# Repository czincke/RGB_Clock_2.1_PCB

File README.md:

# RGB_Clock_2.1_PCB
Updated RGB Clock using Adafruit products

Clock using four 7 segment RGB LEDs, three 24 channel PWM (TLC5973), RTC (DS3231), & Trinket (ATTiny85).

Materials:
* 1 x PCB
  * PCB	Clock_v2.1.brd
* 4 x RGB 7-Segment Digit
  * Product: https://www.adafruit.com/products/1399
* 3 x 24-Channel 12-bit PWM LED Driver (TLC5973)
  * Product: https://www.adafruit.com/products/1429
  * Tutorial: https://learn.adafruit.com/tlc5947-tlc59711-pwm-led-driver-breakout
* 1 x DS3231 Precision RTC Breakout
  * Product: https://www.adafruit.com/products/3013
  * Tutorial: https://learn.adafruit.com/adafruit-ds3231-precision-rtc-breakout/
* 1 x Adafruit Trinket - Mini Microcontroller - 5V Logic (ATTiny85)
  * Product: https://www.adafruit.com/products/1501
  * Tutorial: https://learn.adafruit.com/introducing-trinket

See: https://github.com/czincke/RGB_Clock_2.1_Code for Software Code.

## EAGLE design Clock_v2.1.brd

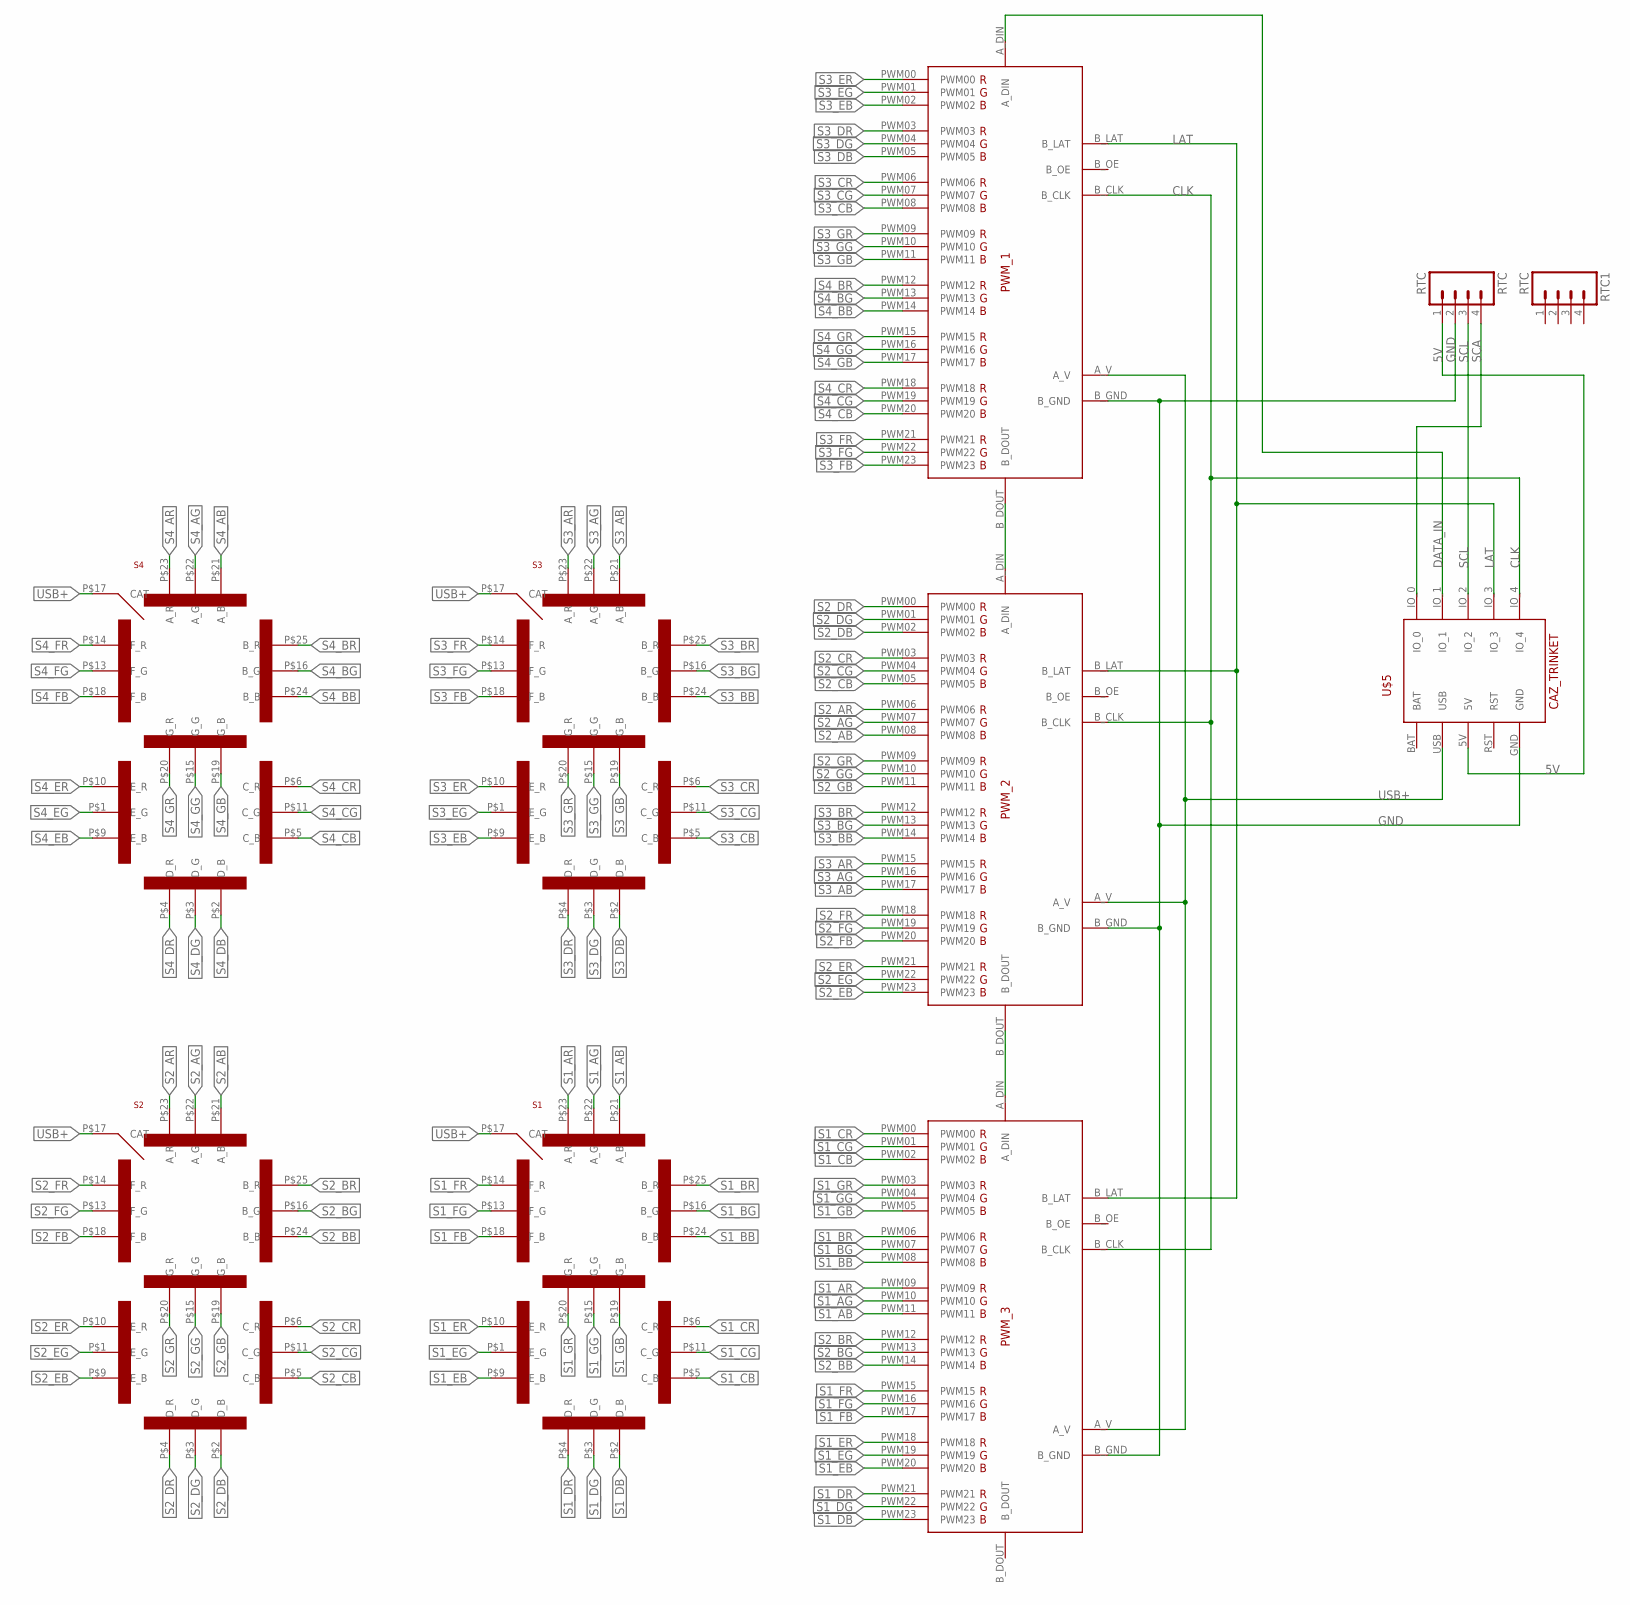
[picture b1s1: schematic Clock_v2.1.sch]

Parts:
PWM_1, PWM_2, PWM_3: CAZ_24PWM_DRIVER_MINIMAL
RTC, RTC1: RTC; 1X04_NO_SILK
S1, S2, S3, S4: CAZ_7SEGMENT_RGB_LEDBACKSIDE_MOUNT; CAZ_7SEGMENT_RGB_LED
U$5: CAZ_TRINKET

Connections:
5V: RTC.1, U$5.5V
CLK: PWM_1.B_CLK, PWM_2.B_CLK, PWM_3.B_CLK, U$5.IO_4
DATA_IN: PWM_1.A_DIN, U$5.IO_1
GND: PWM_1.B_GND, PWM_2.B_GND, PWM_3.B_GND, RTC.2, U$5.GND
LAT: PWM_1.B_LAT, PWM_2.B_LAT, PWM_3.B_LAT, U$5.IO_3
unnamed: PWM_1.B_DOUT, PWM_2.A_DIN
unnamed: PWM_2.B_DOUT, PWM_3.A_DIN
S1_AB: PWM_3.PWM11, S1.P$21 (A_B)
S1_AG: PWM_3.PWM10, S1.P$22 (A_G)
S1_AR: PWM_3.PWM09, S1.P$23 (A_R)
S1_BB: PWM_3.PWM08, S1.P$24 (B_B)
S1_BG: PWM_3.PWM07, S1.P$16 (B_G)
S1_BR: PWM_3.PWM06, S1.P$25 (B_R)
S1_CB: PWM_3.PWM02, S1.P$5 (C_B)
S1_CG: PWM_3.PWM01, S1.P$11 (C_G)
S1_CR: PWM_3.PWM00, S1.P$6 (C_R)
S1_DB: PWM_3.PWM23, S1.P$2 (D_B)
S1_DG: PWM_3.PWM22, S1.P$3 (D_G)
S1_DR: PWM_3.PWM21, S1.P$4 (D_R)
S1_EB: PWM_3.PWM20, S1.P$9 (E_B)
S1_EG: PWM_3.PWM19, S1.P$1 (E_G)
S1_ER: PWM_3.PWM18, S1.P$10 (E_R)
S1_FB: PWM_3.PWM17, S1.P$18 (F_B)
S1_FG: PWM_3.PWM16, S1.P$13 (F_G)
S1_FR: PWM_3.PWM15, S1.P$14 (F_R)
S1_GB: PWM_3.PWM05, S1.P$19 (G_B)
S1_GG: PWM_3.PWM04, S1.P$15 (G_G)
S1_GR: PWM_3.PWM03, S1.P$20 (G_R)
S2_AB: PWM_2.PWM08, S2.P$21 (A_B)
S2_AG: PWM_2.PWM07, S2.P$22 (A_G)
S2_AR: PWM_2.PWM06, S2.P$23 (A_R)
S2_BB: PWM_3.PWM14, S2.P$24 (B_B)
S2_BG: PWM_3.PWM13, S2.P$16 (B_G)
S2_BR: PWM_3.PWM12, S2.P$25 (B_R)
S2_CB: PWM_2.PWM05, S2.P$5 (C_B)
S2_CG: PWM_2.PWM04, S2.P$11 (C_G)
S2_CR: PWM_2.PWM03, S2.P$6 (C_R)
S2_DB: PWM_2.PWM02, S2.P$2 (D_B)
S2_DG: PWM_2.PWM01, S2.P$3 (D_G)
S2_DR: PWM_2.PWM00, S2.P$4 (D_R)
S2_EB: PWM_2.PWM23, S2.P$9 (E_B)
S2_EG: PWM_2.PWM22, S2.P$1 (E_G)
S2_ER: PWM_2.PWM21, S2.P$10 (E_R)
S2_FB: PWM_2.PWM20, S2.P$18 (F_B)
S2_FG: PWM_2.PWM19, S2.P$13 (F_G)
S2_FR: PWM_2.PWM18, S2.P$14 (F_R)
S2_GB: PWM_2.PWM11, S2.P$19 (G_B)
S2_GG: PWM_2.PWM10, S2.P$15 (G_G)
S2_GR: PWM_2.PWM09, S2.P$20 (G_R)
S3_AB: PWM_2.PWM17, S3.P$21 (A_B)
S3_AG: PWM_2.PWM16, S3.P$22 (A_G)
S3_AR: PWM_2.PWM15, S3.P$23 (A_R)
S3_BB: PWM_2.PWM14, S3.P$24 (B_B)
S3_BG: PWM_2.PWM13, S3.P$16 (B_G)
S3_BR: PWM_2.PWM12, S3.P$25 (B_R)
S3_CB: PWM_1.PWM08, S3.P$5 (C_B)
S3_CG: PWM_1.PWM07, S3.P$11 (C_G)
S3_CR: PWM_1.PWM06, S3.P$6 (C_R)
S3_DB: PWM_1.PWM05, S3.P$2 (D_B)
S3_DG: PWM_1.PWM04, S3.P$3 (D_G)
S3_DR: PWM_1.PWM03, S3.P$4 (D_R)
S3_EB: PWM_1.PWM02, S3.P$9 (E_B)
S3_EG: PWM_1.PWM01, S3.P$1 (E_G)
S3_ER: PWM_1.PWM00, S3.P$10 (E_R)
S3_FB: PWM_1.PWM23, S3.P$18 (F_B)
S3_FG: PWM_1.PWM22, S3.P$13 (F_G)
S3_FR: PWM_1.PWM21, S3.P$14 (F_R)
S3_GB: PWM_1.PWM11, S3.P$19 (G_B)
S3_GG: PWM_1.PWM10, S3.P$15 (G_G)
S3_GR: PWM_1.PWM09, S3.P$20 (G_R)
S4_AB: S4.P$21 (A_B)
S4_AG: S4.P$22 (A_G)
S4_AR: S4.P$23 (A_R)
S4_BB: PWM_1.PWM14, S4.P$24 (B_B)
S4_BG: PWM_1.PWM13, S4.P$16 (B_G)
S4_BR: PWM_1.PWM12, S4.P$25 (B_R)
S4_CB: PWM_1.PWM20, S4.P$5 (C_B)
S4_CG: PWM_1.PWM19, S4.P$11 (C_G)
S4_CR: PWM_1.PWM18, S4.P$6 (C_R)
S4_DB: S4.P$2 (D_B)
S4_DG: S4.P$3 (D_G)
S4_DR: S4.P$4 (D_R)
S4_EB: S4.P$9 (E_B)
S4_EG: S4.P$1 (E_G)
S4_ER: S4.P$10 (E_R)
S4_FB: S4.P$18 (F_B)
S4_FG: S4.P$13 (F_G)
S4_FR: S4.P$14 (F_R)
S4_GB: PWM_1.PWM17, S4.P$19 (G_B)
S4_GG: PWM_1.PWM16, S4.P$15 (G_G)
S4_GR: PWM_1.PWM15, S4.P$20 (G_R)
SCA: RTC.4, U$5.IO_0
SCL: RTC.3, U$5.IO_2
USB+: PWM_1.A_V, PWM_2.A_V, PWM_3.A_V, S1.P$17 (CAT), S2.P$17 (CAT), S3.P$17 (CAT), S4.P$17 (CAT), U$5.USB

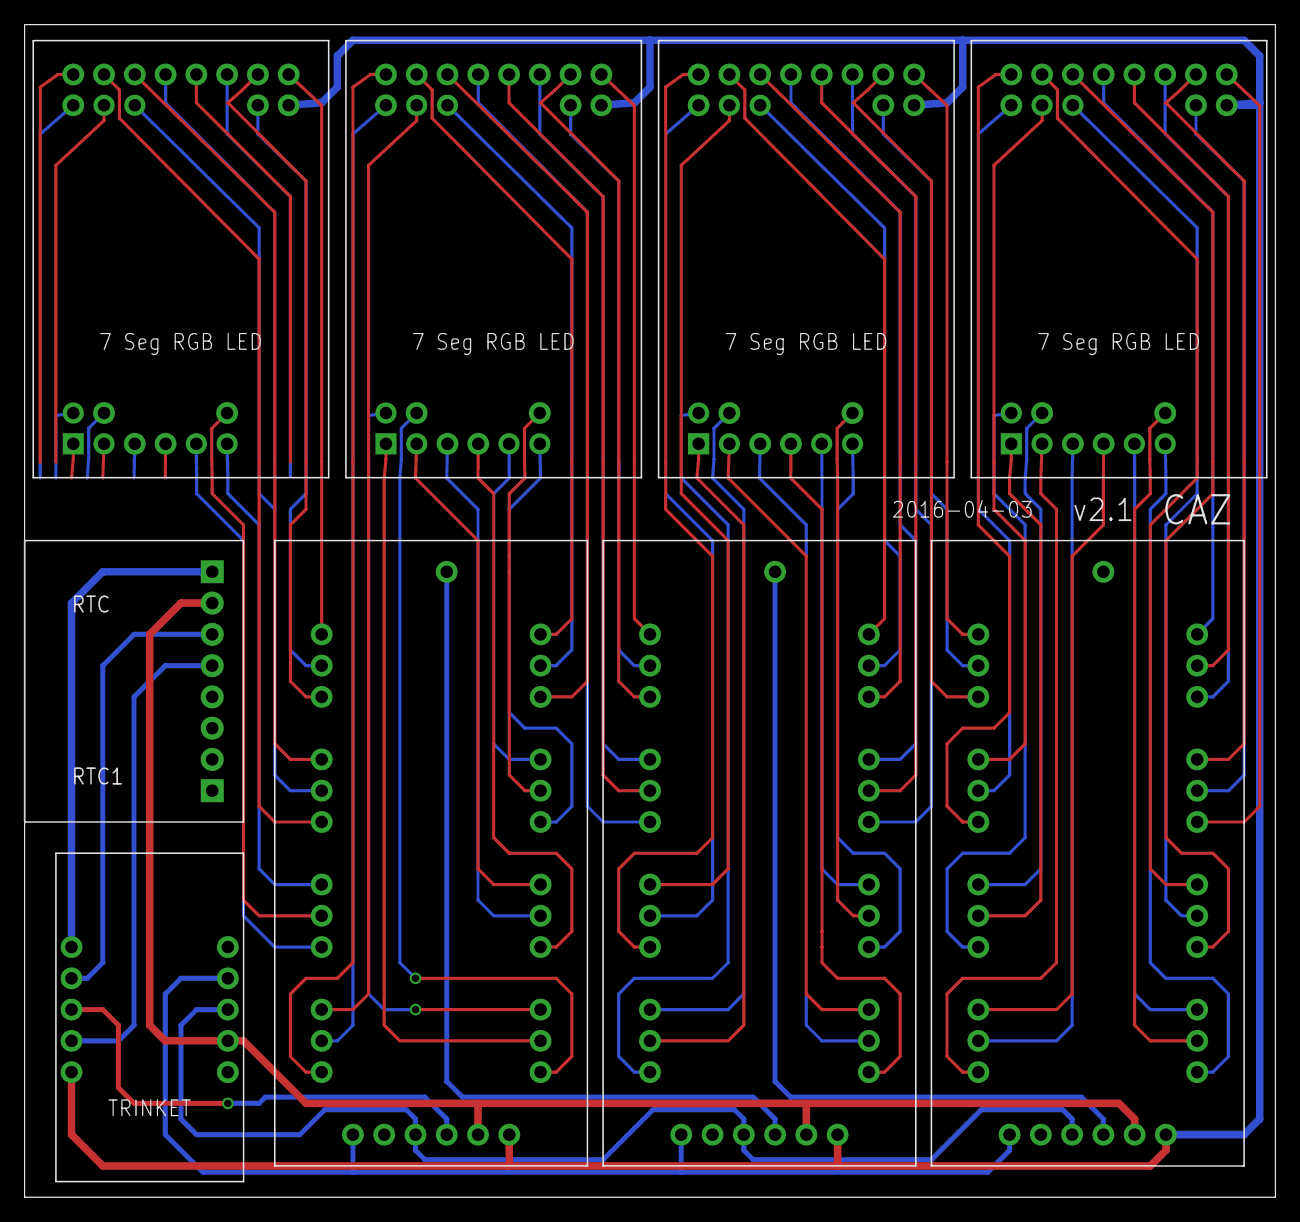
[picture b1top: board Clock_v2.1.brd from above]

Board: 2 copper layers, 101.6 x 95.2 mm, 10 parts (0 on the bottom side), 82 nets.

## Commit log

2016-04-03 :neckbeard: Added .gitattributes & .gitignore files
2016-04-03 Updated RGB Clock using Adafruit products
    Clock using four 7 segment RGB LEDs, three 24 channel PWM (TLC5973), RTC
    (DS3231), & Trinket (ATTiny85).
2016-04-03 Revert "Updated RGB Clock using Adafruit products"
    This reverts commit 65e5b0dab4c35bce87b37392f05b60f3e57cfe0f.
2016-04-03 Real upload
2016-04-03 pdf of Eagle design of PCB
2016-04-03 Added Parts list
2016-04-04 added datasheets

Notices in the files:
parts and their libraries:
SparkFun-Connectors: Licensing: CC v3.0 Share-Alike You are welcome to use this library for commercial purposes.
